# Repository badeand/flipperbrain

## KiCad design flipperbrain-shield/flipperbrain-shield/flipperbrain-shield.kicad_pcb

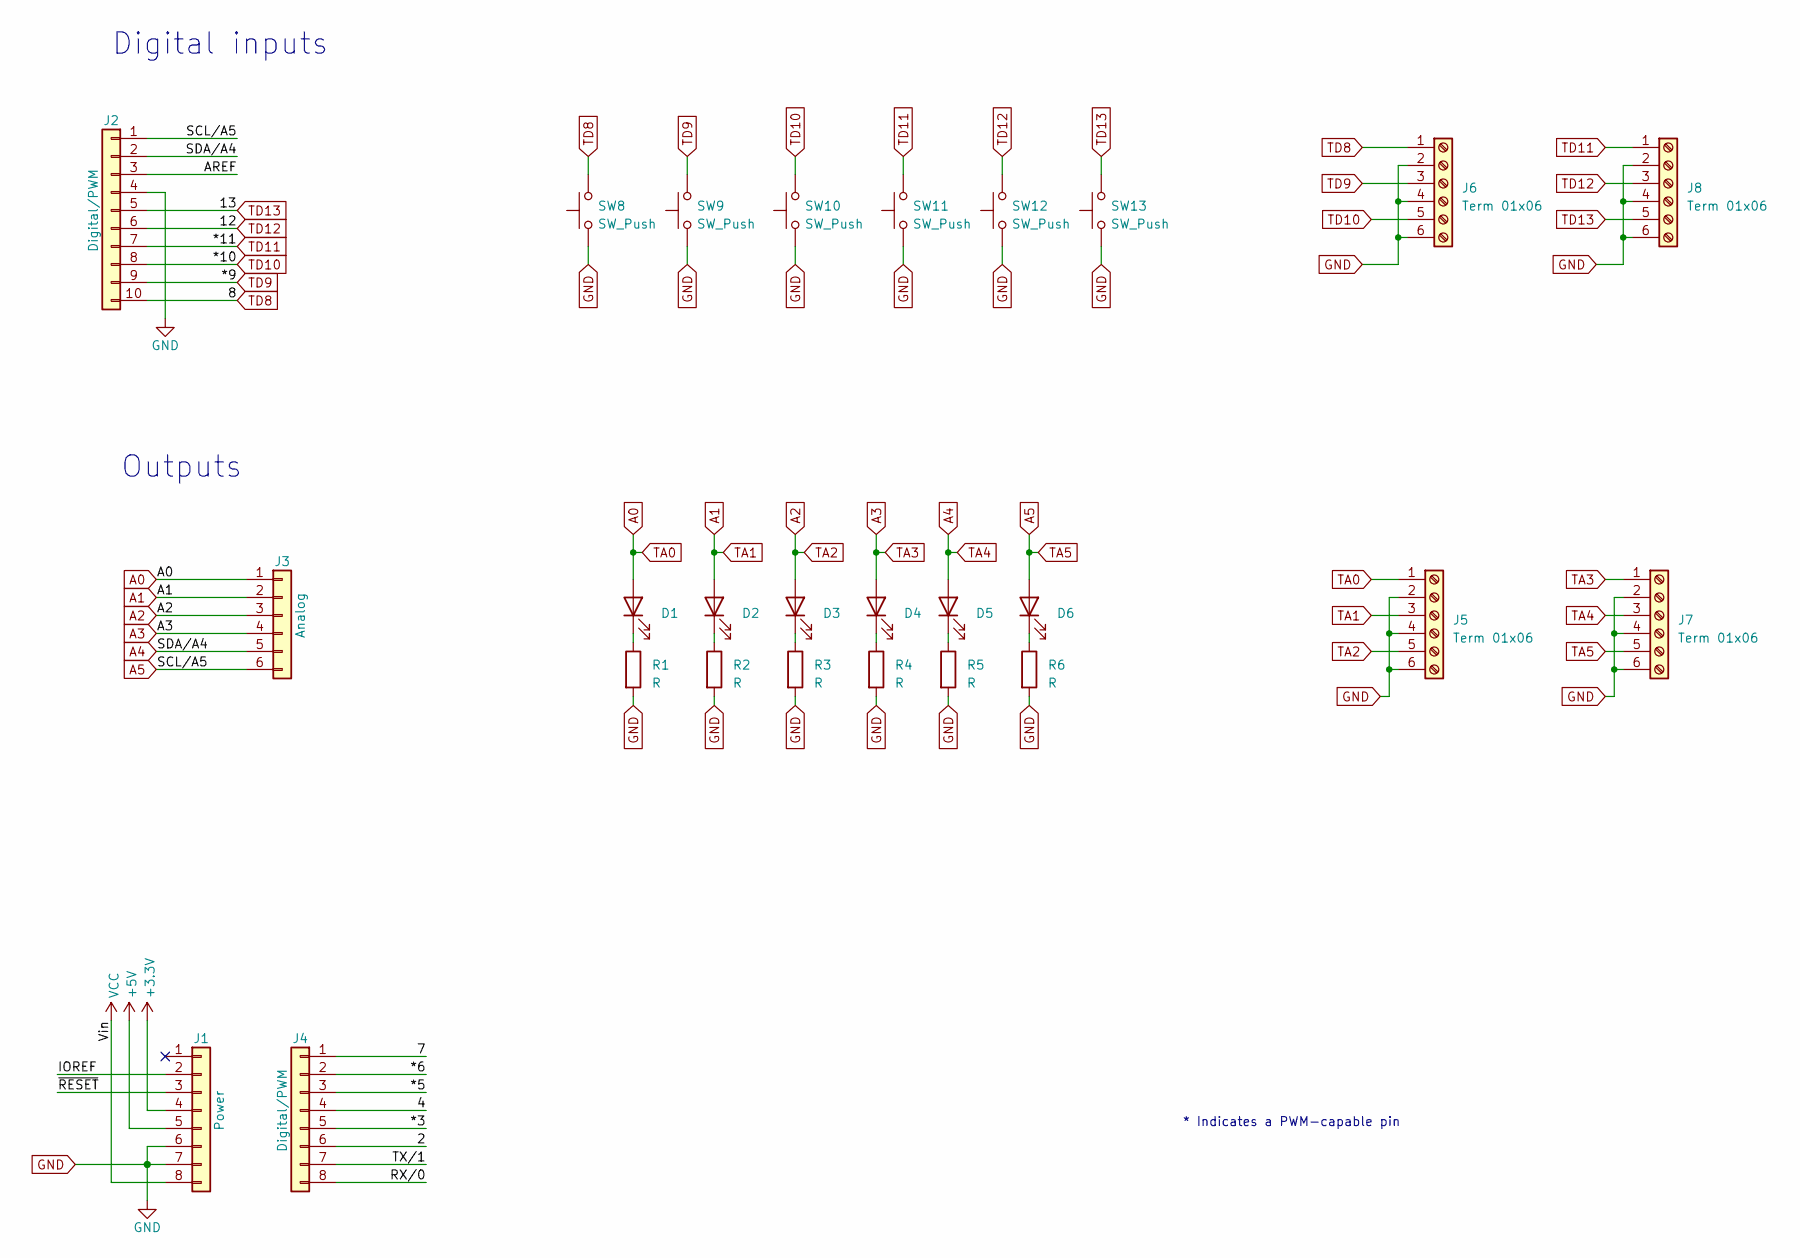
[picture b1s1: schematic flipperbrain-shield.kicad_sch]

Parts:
D1, D2, D3, D4, D5, D6: LED; LED_D5.0mm
J1: Power; PinHeader_1x08_P2.54mm_Vertical
J2: Digital/PWM; PinHeader_1x10_P2.54mm_Vertical
J3: Analog; PinHeader_1x06_P2.54mm_Vertical
J4: Digital/PWM; PinHeader_1x08_P2.54mm_Vertical
J5, J6, J7, J8: Term 01x06; TerminalBlock_Phoenix_PT-1,5-6-3.5-H_1x06_P3.50mm_Horizontal
R1, R2, R3, R4, R5, R6: R; R_Axial_DIN0207_L6.3mm_D2.5mm_P7.62mm_Horizontal
SW8, SW9, SW10, SW11, SW12, SW13: SW_Push; SW_PUSH_6mm

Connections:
+3V3: J1.4
+5V: J1.5
/2: J4.6
/4: J4.4
/7: J4.1
/*3: J4.5
/*5: J4.3
/*6: J4.2
/AREF: J2.3
/IOREF: J1.2
/RX/0: J4.8
/TX/1: J4.7
/~RESET: J1.3
A0: D1.2 (A), J3.1, J5.1
A1: D2.2 (A), J3.2, J5.3
A2: D3.2 (A), J3.3, J5.5
A3: D4.2 (A), J3.4, J7.1
A4: D5.2 (A), J2.2, J3.5, J7.3
A5: D6.2 (A), J2.1, J3.6, J7.5
GND: J1.6, J1.7, J2.4, J5.2, J5.4, J5.6, J6.2, J6.4, J6.6, J7.2, J7.4, J7.6, J8.2, J8.4, J8.6, R1.2, R2.2, R3.2, R4.2, R5.2, R6.2, SW8.1, SW9.1, SW10.1, SW11.1, SW12.1, SW13.1
unnamed: D1.1 (K), R1.1
unnamed: D2.1 (K), R2.1
unnamed: D3.1 (K), R3.1
unnamed: D4.1 (K), R4.1
unnamed: D5.1 (K), R5.1
unnamed: D6.1 (K), R6.1
TD8: J2.10, J6.1, SW8.2
TD9: J2.9, J6.3, SW9.2
TD10: J2.8, J6.5, SW10.2
TD11: J2.7, J8.1, SW11.2
TD12: J2.6, J8.3, SW12.2
TD13: J2.5, J8.5, SW13.2
VCC: J1.8

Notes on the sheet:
Outputs
Digital inputs
* Indicates a PWM-capable pin

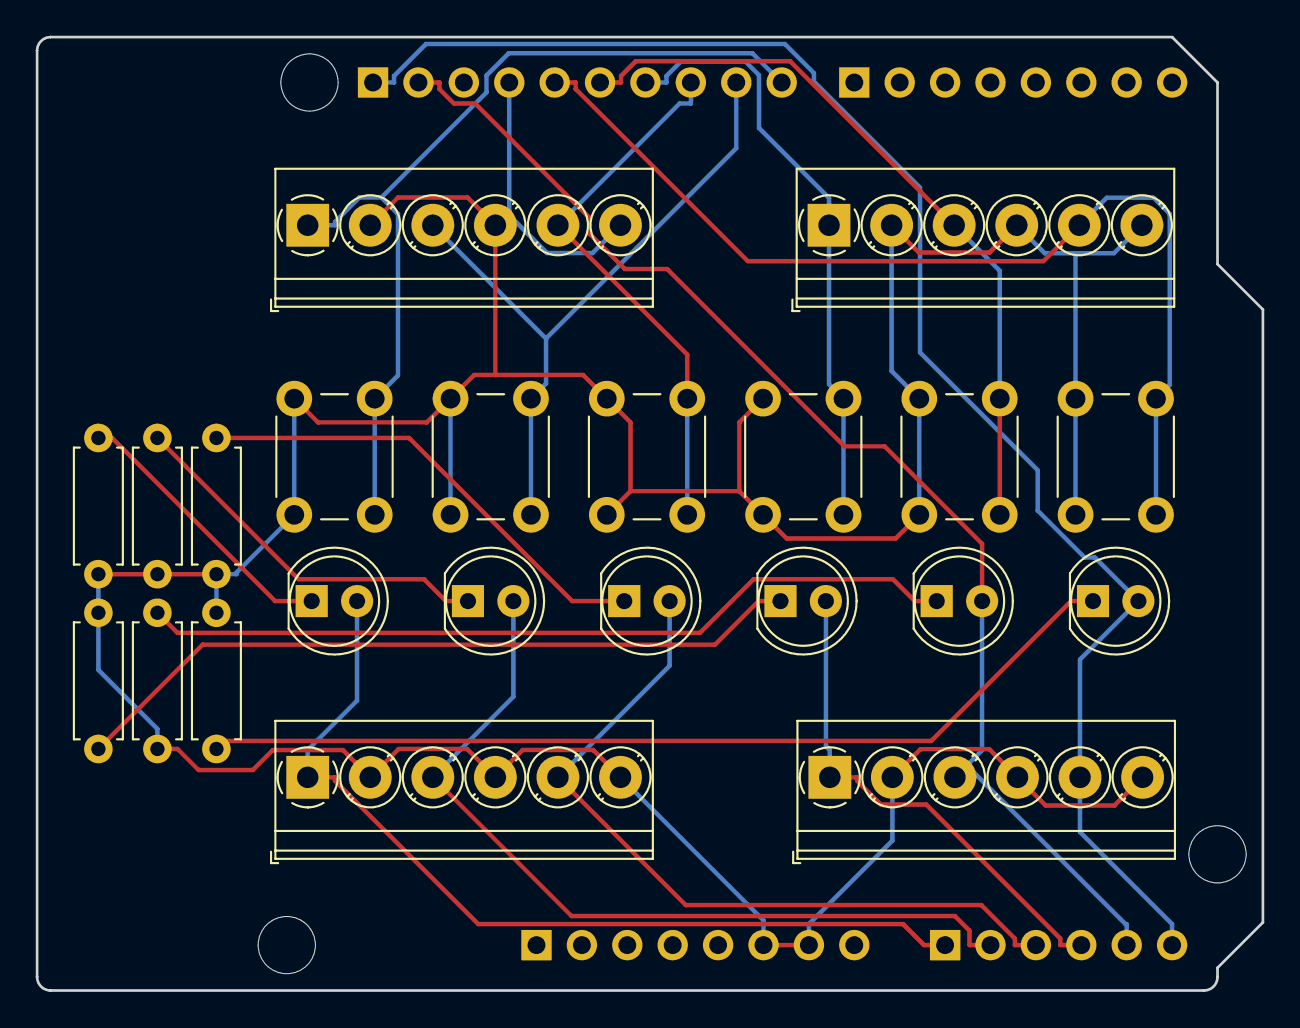
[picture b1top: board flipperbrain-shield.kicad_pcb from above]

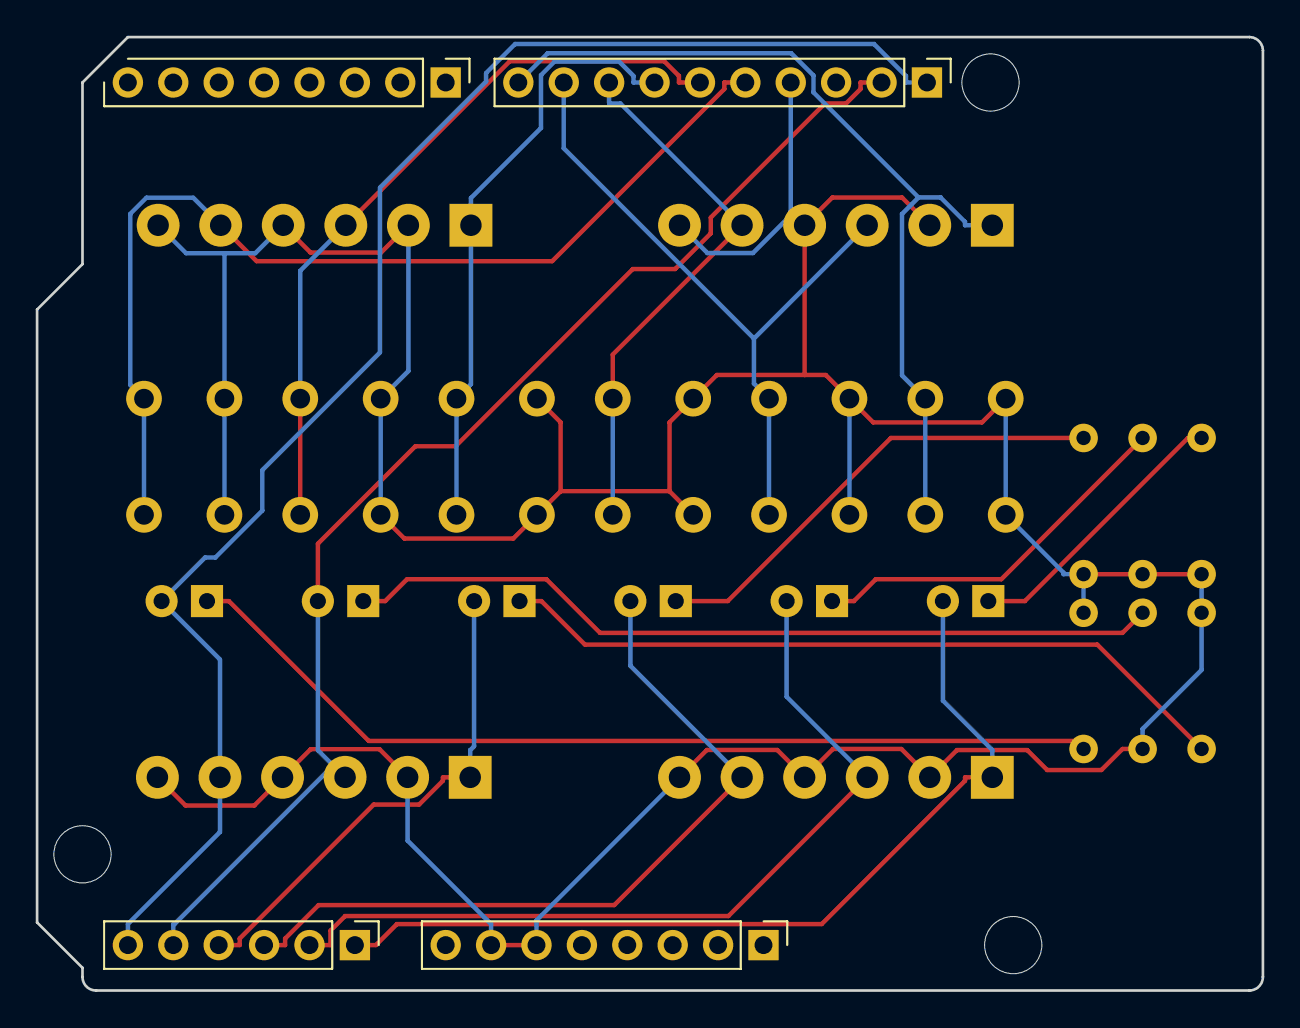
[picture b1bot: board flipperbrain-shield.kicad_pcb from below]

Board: 2 copper layers, 68.6 x 53.3 mm, 29 parts (4 on the bottom side), 19 nets.

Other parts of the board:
MH1, MH2, MH4: MountingHole_3.2mm

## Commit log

2023-07-25 init
2023-09-19 tre innganger og tre utganger.
2023-10-03 with scoring
2023-10-03 pressed state
